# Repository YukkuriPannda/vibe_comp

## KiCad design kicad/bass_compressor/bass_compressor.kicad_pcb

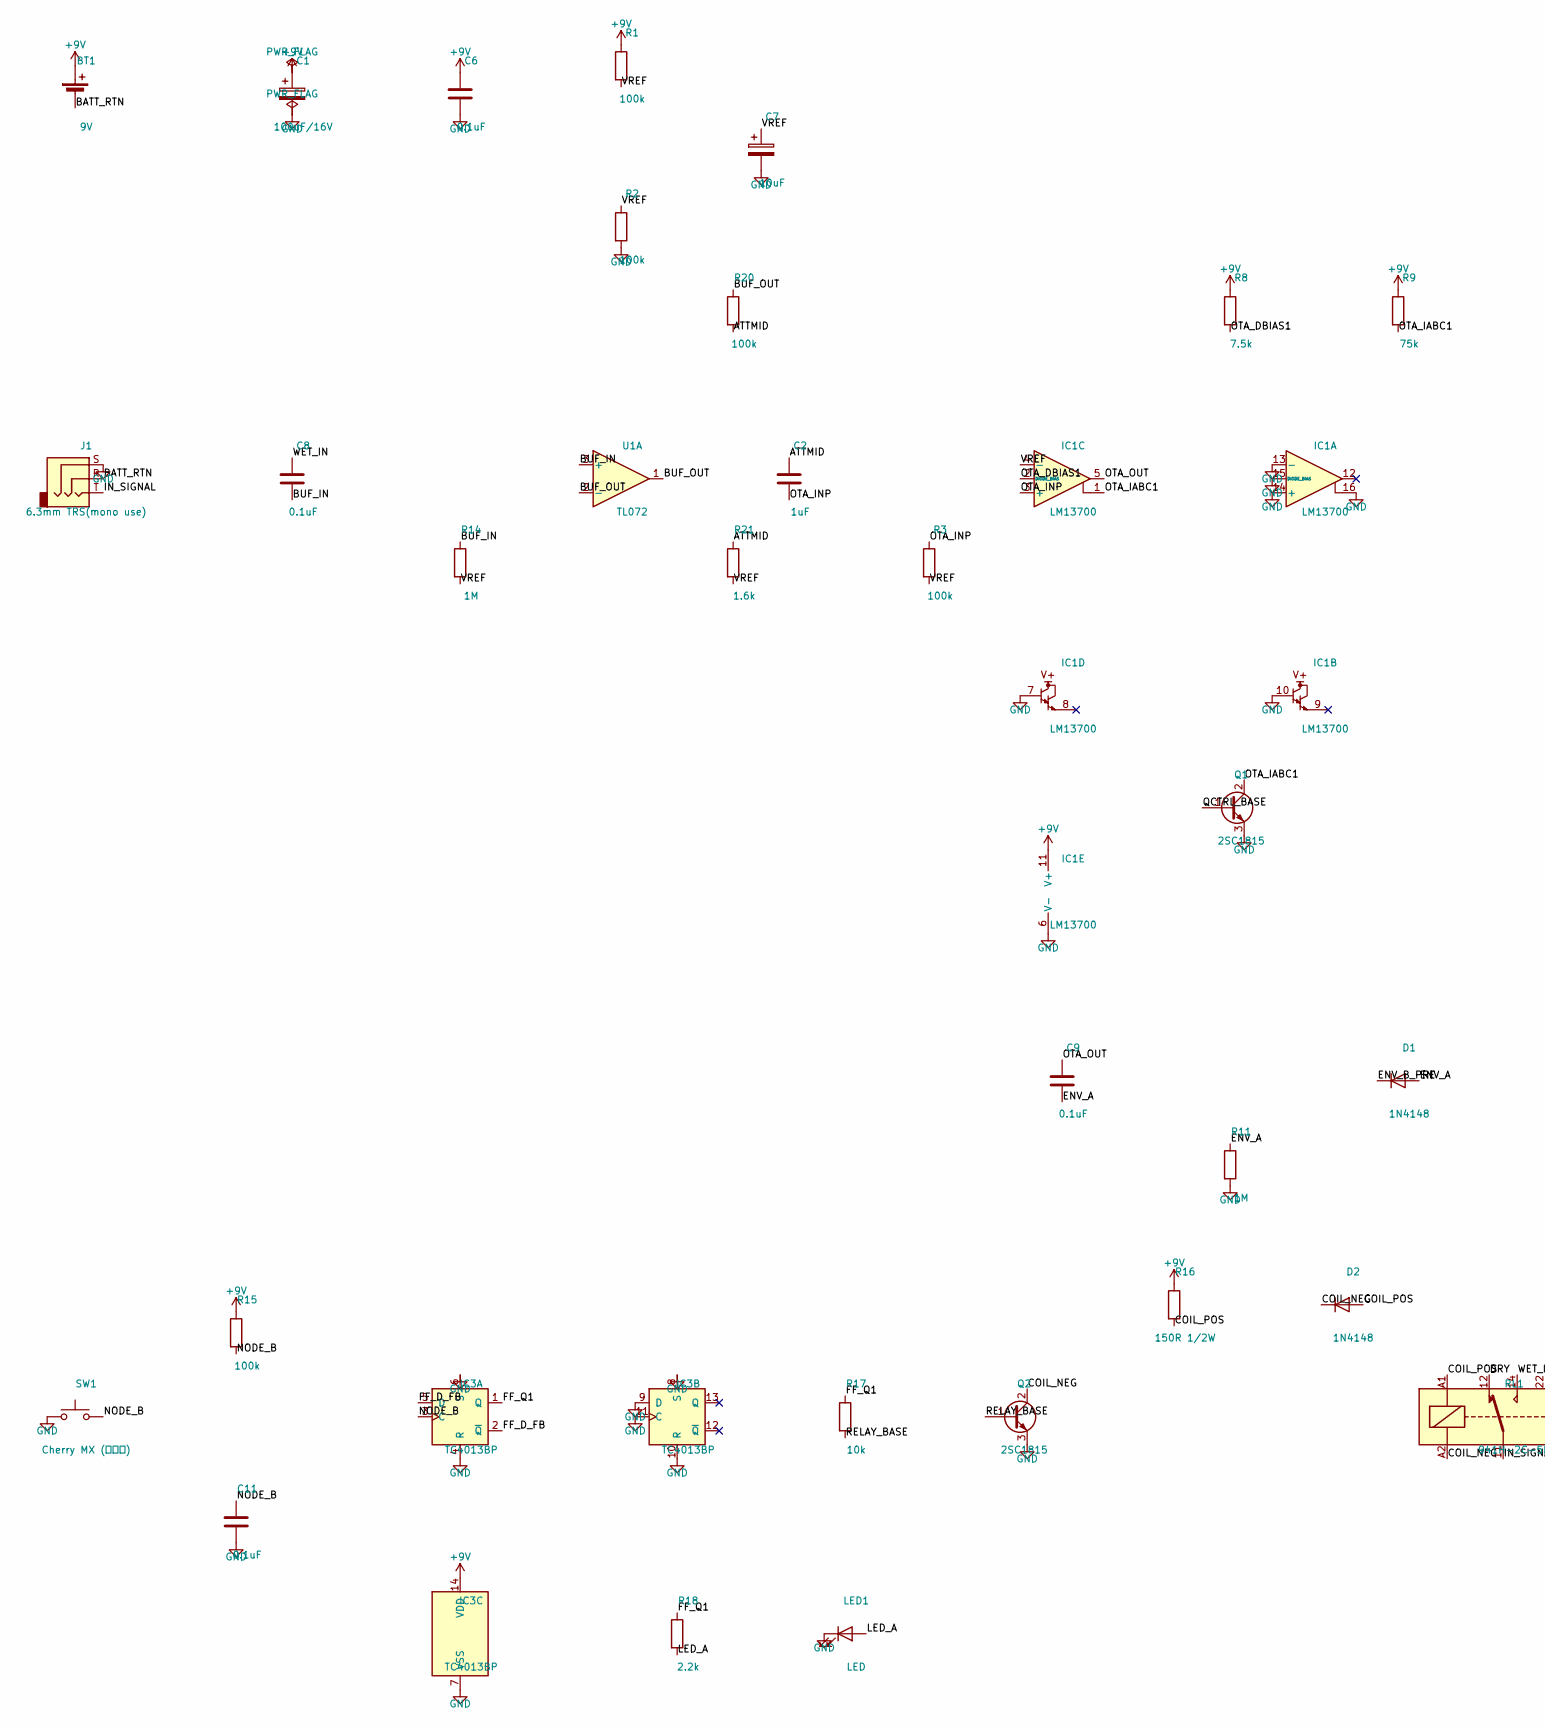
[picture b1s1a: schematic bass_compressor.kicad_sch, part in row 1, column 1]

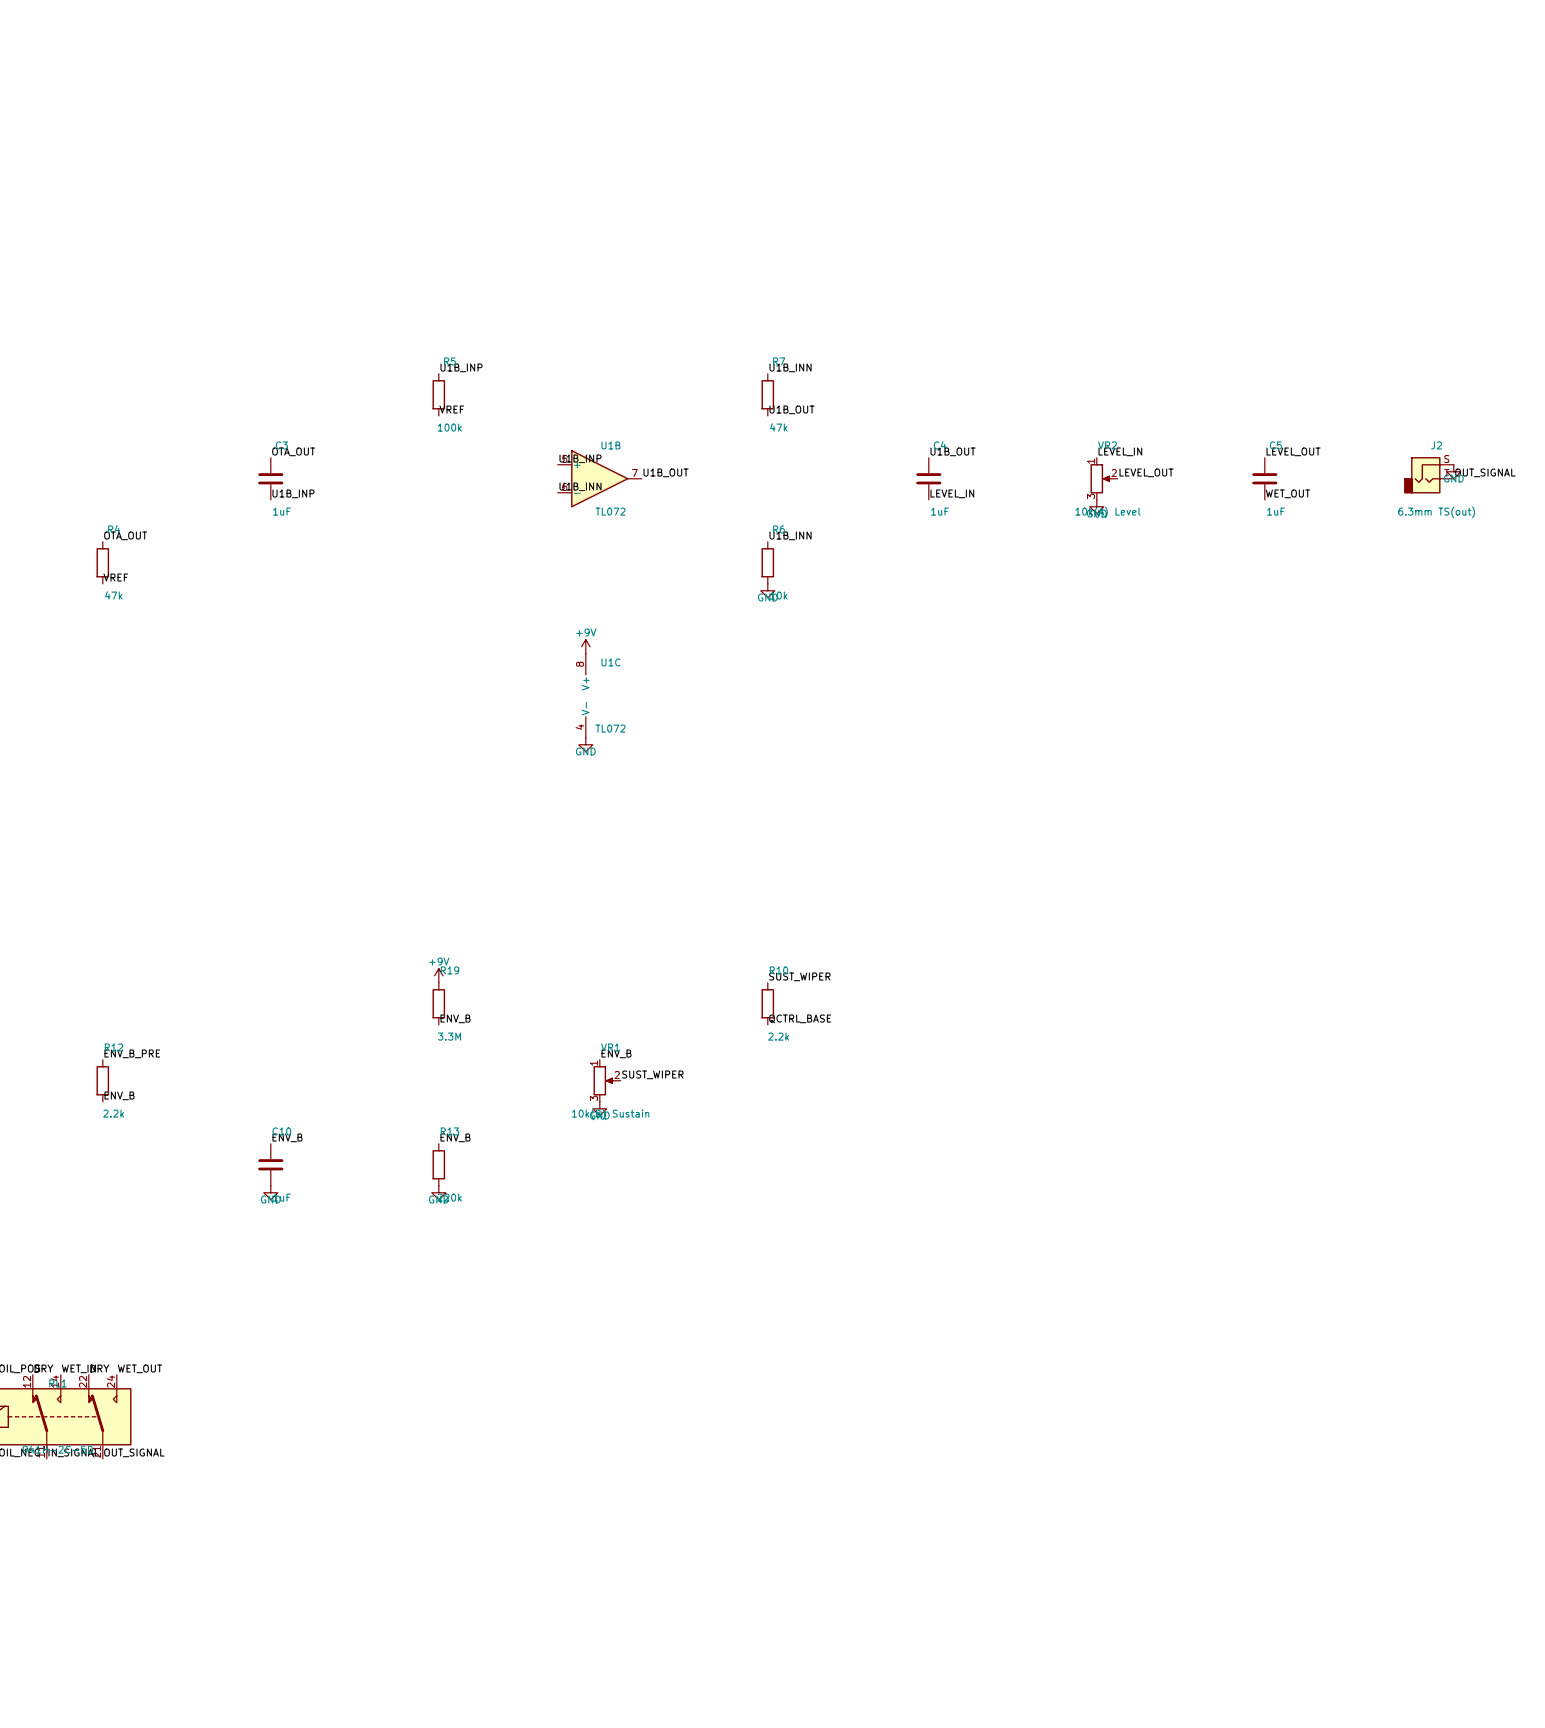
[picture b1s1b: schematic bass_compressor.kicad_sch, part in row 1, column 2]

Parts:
BT1: 9V; PinHeader_1x02_P2.54mm_Vertical
C1: 100uF/16V; CP_Radial_D6.3mm_P2.50mm
C2, C3, C4, C5, C10: 1uF; C_Radial_D5.0mm_H11.0mm_P2.00mm
C6: 0.1uF; C_Disc_D3.0mm_W2.0mm_P2.50mm
C7: 10uF; CP_Radial_D5.0mm_P2.00mm
C8, C9, C11: 0.1uF; C_Radial_D5.0mm_H11.0mm_P2.00mm
D1, D2: 1N4148; D_DO-35_SOD27_P10.16mm_Horizontal
IC1: LM13700; DIP-16_W7.62mm_Socket
IC3: TC4013BP; DIP-14_W7.62mm_Socket
J1: 6.3mm TRS(mono use); Jack_6.35mm_Neutrik_NRJ6HF_Horizontal
J2: 6.3mm TS(out); Jack_6.35mm_Neutrik_NMJ4HCD2_Horizontal
LED1: LED; LED_D3.0mm
Q1, Q2: 2SC1815; TO-92
R1, R2, R3, R5, R15, R20: 100k; R_Axial_DIN0207_L6.3mm_D2.5mm_P10.16mm_Horizontal
R4, R7: 47k; R_Axial_DIN0207_L6.3mm_D2.5mm_P10.16mm_Horizontal
R6, R17: 10k; R_Axial_DIN0207_L6.3mm_D2.5mm_P10.16mm_Horizontal
R8: 7.5k; R_Axial_DIN0207_L6.3mm_D2.5mm_P10.16mm_Horizontal
R9: 75k; R_Axial_DIN0207_L6.3mm_D2.5mm_P10.16mm_Horizontal
R10, R12, R18: 2.2k; R_Axial_DIN0207_L6.3mm_D2.5mm_P10.16mm_Horizontal
R11, R14: 1M; R_Axial_DIN0207_L6.3mm_D2.5mm_P10.16mm_Horizontal
R13: 220k; R_Axial_DIN0207_L6.3mm_D2.5mm_P10.16mm_Horizontal
R16: 150R 1/2W; R_Axial_DIN0309_L9.0mm_D3.2mm_P12.70mm_Horizontal
R19: 3.3M; R_Axial_DIN0207_L6.3mm_D2.5mm_P10.16mm_Horizontal
R21: 1.6k; R_Axial_DIN0207_L6.3mm_D2.5mm_P10.16mm_Horizontal
RL1: 941H-2C-5D; Relay_DPDT_Schrack-RT2-FormC_RM5mm
SW1: Cherry MX (手持ち); SW_Cherry_MX_1.00u_PCB
U1: TL072; DIP-8_W7.62mm_Socket
VR1: 10k(B) Sustain; Potentiometer_Alps_RK09K_Single_Vertical
VR2: 10k(A) Level; Potentiometer_Alps_RK09K_Single_Vertical

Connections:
ATTMID: C2.1, R20.2, R21.1
BATT_RTN: BT1.2 (-), J1.R
BUF_IN: C8.2, R14.1, U1.3 (+)
BUF_OUT: R20.1, U1.1, U1.2 (-)
COIL_NEG: D2.1 (K), Q2.2 (C), RL1.A2
COIL_POS: D2.2 (A), R16.2, RL1.A1
DRY: RL1.12, RL1.22
ENV_A: C9.2, D1.2 (A), R11.1
ENV_B: C10.1, R12.2, R13.1, R19.2, VR1.1
ENV_B_PRE: D1.1 (K), R12.1
FF_D_FB: IC3.2 (~Q), IC3.5 (D)
FF_Q1: IC3.1 (Q), R17.1, R18.1
GND: C1.2, C6.2, C7.2, C10.2, C11.2, IC1.6 (V-), IC1.7, IC1.10, IC1.13 (-), IC1.14 (+), IC1.15 (DIODE_BIAS), IC1.16, IC3.4 (R), IC3.6 (S), IC3.7 (VSS), IC3.8 (S), IC3.9 (D), IC3.10 (R), IC3.11 (C), J1.S, J2.S, LED1.1 (K), Q1.3 (E), Q2.3 (E), R2.2, R6.2, R11.2, R13.2, SW1.1, U1.4 (V-), VR1.3, VR2.3
IN_SIGNAL: J1.T, RL1.11
LED_A: LED1.2 (A), R18.2
LEVEL_IN: C4.2, VR2.1
LEVEL_OUT: C5.1, VR2.2
NODE_B: C11.1, IC3.3 (C), R15.2, SW1.2
OTA_DBIAS1: IC1.2 (DIODE_BIAS), R8.2
OTA_IABC1: IC1.1, Q1.2 (C), R9.2
OTA_INP: C2.2, IC1.3 (+), R3.1
OTA_OUT: C3.1, C9.1, IC1.5, R4.1
OUT_SIGNAL: J2.T, RL1.21
QCTRL_BASE: Q1.1 (B), R10.2
RELAY_BASE: Q2.1 (B), R17.2
SUST_WIPER: R10.1, VR1.2
U1B_INN: R6.1, R7.1, U1.6 (-)
U1B_INP: C3.2, R5.1, U1.5 (+)
U1B_OUT: C4.1, R7.2, U1.7
VPLUS: BT1.1 (+), C1.1, C6.1, IC1.11 (V+), IC3.14 (VDD), R1.1, R8.1, R9.1, R15.1, R16.1, R19.1, U1.8 (V+)
VREF: C7.1, IC1.4 (-), R1.2, R2.1, R3.2, R4.2, R5.2, R14.2, R21.2
WET_IN: C8.1, RL1.14
WET_OUT: C5.2, RL1.24

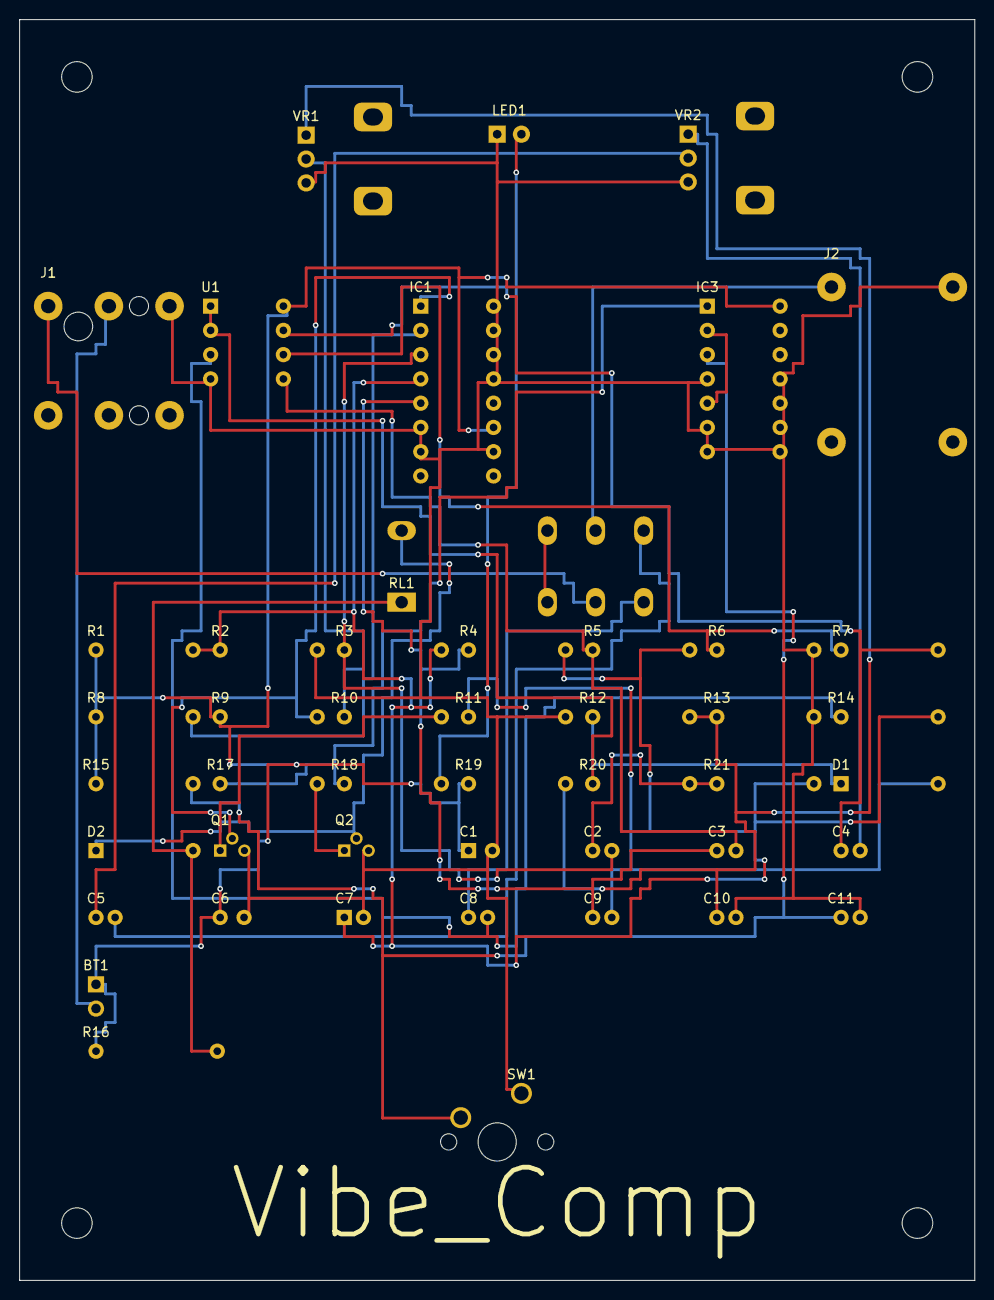
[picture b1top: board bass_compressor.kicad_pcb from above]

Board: 2 copper layers, 100.0 x 132.0 mm, 51 parts (0 on the bottom side), 33 nets.

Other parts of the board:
MH1, MH2, MH3, MH4: MountingHole_3.2mm_M3

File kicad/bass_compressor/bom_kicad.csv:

"Refs","Value","Footprint","Qty","DNP"
"BT1","9V","Connector_PinHeader_2.54mm:PinHeader_1x02_P2.54mm_Vertical","1",""
"C1","100uF/16V","Capacitor_THT:CP_Radial_D6.3mm_P2.50mm","1",""
"C2","1uF","Capacitor_THT:C_Radial_D5.0mm_H11.0mm_P2.00mm","1",""
"C3","1uF","Capacitor_THT:C_Radial_D5.0mm_H11.0mm_P2.00mm","1",""
"C4","1uF","Capacitor_THT:C_Radial_D5.0mm_H11.0mm_P2.00mm","1",""
"C5","1uF","Capacitor_THT:C_Radial_D5.0mm_H11.0mm_P2.00mm","1",""
"C6","0.1uF","Capacitor_THT:C_Disc_D3.0mm_W2.0mm_P2.50mm","1",""
"C7","10uF","Capacitor_THT:CP_Radial_D5.0mm_P2.00mm","1",""
"C8","0.1uF","Capacitor_THT:C_Radial_D5.0mm_H11.0mm_P2.00mm","1",""
"C9","0.1uF","Capacitor_THT:C_Radial_D5.0mm_H11.0mm_P2.00mm","1",""
"C10","1uF","Capacitor_THT:C_Radial_D5.0mm_H11.0mm_P2.00mm","1",""
"C11","0.1uF","Capacitor_THT:C_Radial_D5.0mm_H11.0mm_P2.00mm","1",""
"D1","1N4148","Diode_THT:D_DO-35_SOD27_P10.16mm_Horizontal","1",""
"D2","1N4148","Diode_THT:D_DO-35_SOD27_P10.16mm_Horizontal","1",""
"IC1","LM13700","Package_DIP:DIP-16_W7.62mm_Socket","1",""
"IC3","TC4013BP","Package_DIP:DIP-14_W7.62mm_Socket","1",""
"J1","6.3mm TRS(mono use)","Connector_Audio:Jack_6.35mm_Neutrik_NRJ6HF_Horizontal","1",""
"J2","6.3mm TS(out)","Connector_Audio:Jack_6.35mm_Neutrik_NMJ4HCD2_Horizontal","1",""
"LED1","LED","LED_THT:LED_D3.0mm","1",""
"Q1","2SC1815","Package_TO_SOT_THT:TO-92","1",""
"Q2","2SC1815","Package_TO_SOT_THT:TO-92","1",""
"R1","100k","Resistor_THT:R_Axial_DIN0207_L6.3mm_D2.5mm_P10.16mm_Horizontal","1",""
"R2","100k","Resistor_THT:R_Axial_DIN0207_L6.3mm_D2.5mm_P10.16mm_Horizontal","1",""
"R3","100k","Resistor_THT:R_Axial_DIN0207_L6.3mm_D2.5mm_P10.16mm_Horizontal","1",""
"R4","47k","Resistor_THT:R_Axial_DIN0207_L6.3mm_D2.5mm_P10.16mm_Horizontal","1",""
"R5","100k","Resistor_THT:R_Axial_DIN0207_L6.3mm_D2.5mm_P10.16mm_Horizontal","1",""
"R6","10k","Resistor_THT:R_Axial_DIN0207_L6.3mm_D2.5mm_P10.16mm_Horizontal","1",""
"R7","47k","Resistor_THT:R_Axial_DIN0207_L6.3mm_D2.5mm_P10.16mm_Horizontal","1",""
"R8","7.5k","Resistor_THT:R_Axial_DIN0207_L6.3mm_D2.5mm_P10.16mm_Horizontal","1",""
"R9","75k","Resistor_THT:R_Axial_DIN0207_L6.3mm_D2.5mm_P10.16mm_Horizontal","1",""
"R10","2.2k","Resistor_THT:R_Axial_DIN0207_L6.3mm_D2.5mm_P10.16mm_Horizontal","1",""
"R11","1M","Resistor_THT:R_Axial_DIN0207_L6.3mm_D2.5mm_P10.16mm_Horizontal","1",""
"R12","2.2k","Resistor_THT:R_Axial_DIN0207_L6.3mm_D2.5mm_P10.16mm_Horizontal","1",""
"R13","220k","Resistor_THT:R_Axial_DIN0207_L6.3mm_D2.5mm_P10.16mm_Horizontal","1",""
"R14","1M","Resistor_THT:R_Axial_DIN0207_L6.3mm_D2.5mm_P10.16mm_Horizontal","1",""
"R15","100k","Resistor_THT:R_Axial_DIN0207_L6.3mm_D2.5mm_P10.16mm_Horizontal","1",""
"R16","150R 1/2W","Resistor_THT:R_Axial_DIN0309_L9.0mm_D3.2mm_P12.70mm_Horizontal","1",""
"R17","10k","Resistor_THT:R_Axial_DIN0207_L6.3mm_D2.5mm_P10.16mm_Horizontal","1",""
"R18","2.2k","Resistor_THT:R_Axial_DIN0207_L6.3mm_D2.5mm_P10.16mm_Horizontal","1",""
"R19","3.3M","Resistor_THT:R_Axial_DIN0207_L6.3mm_D2.5mm_P10.16mm_Horizontal","1",""
"R20","100k","Resistor_THT:R_Axial_DIN0207_L6.3mm_D2.5mm_P10.16mm_Horizontal","1",""
"R21","1.6k","Resistor_THT:R_Axial_DIN0207_L6.3mm_D2.5mm_P10.16mm_Horizontal","1",""
"RL1","941H-2C-5D","Relay_THT:Relay_DPDT_Schrack-RT2-FormC_RM5mm","1",""
"SW1","Cherry MX (手持ち)","Button_Switch_Keyboard:SW_Cherry_MX_1.00u_PCB","1",""
"U1","TL072","Package_DIP:DIP-8_W7.62mm_Socket","1",""
"VR1","10k(B) Sustain","Potentiometer_THT:Potentiometer_Alps_RK09K_Single_Vertical","1",""
"VR2","10k(A) Level","Potentiometer_THT:Potentiometer_Alps_RK09K_Single_Vertical","1",""
